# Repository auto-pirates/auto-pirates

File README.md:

# auto-pirates
*Autonomous Boat Project*

This repository contains the documentation of the Autonomous boat project.

You can find --

* Systems Engineering Presentations
* MRSD Presenatation
* Individual Lab Presentations 
* Critical Design Review

and other miscellaneous documents.

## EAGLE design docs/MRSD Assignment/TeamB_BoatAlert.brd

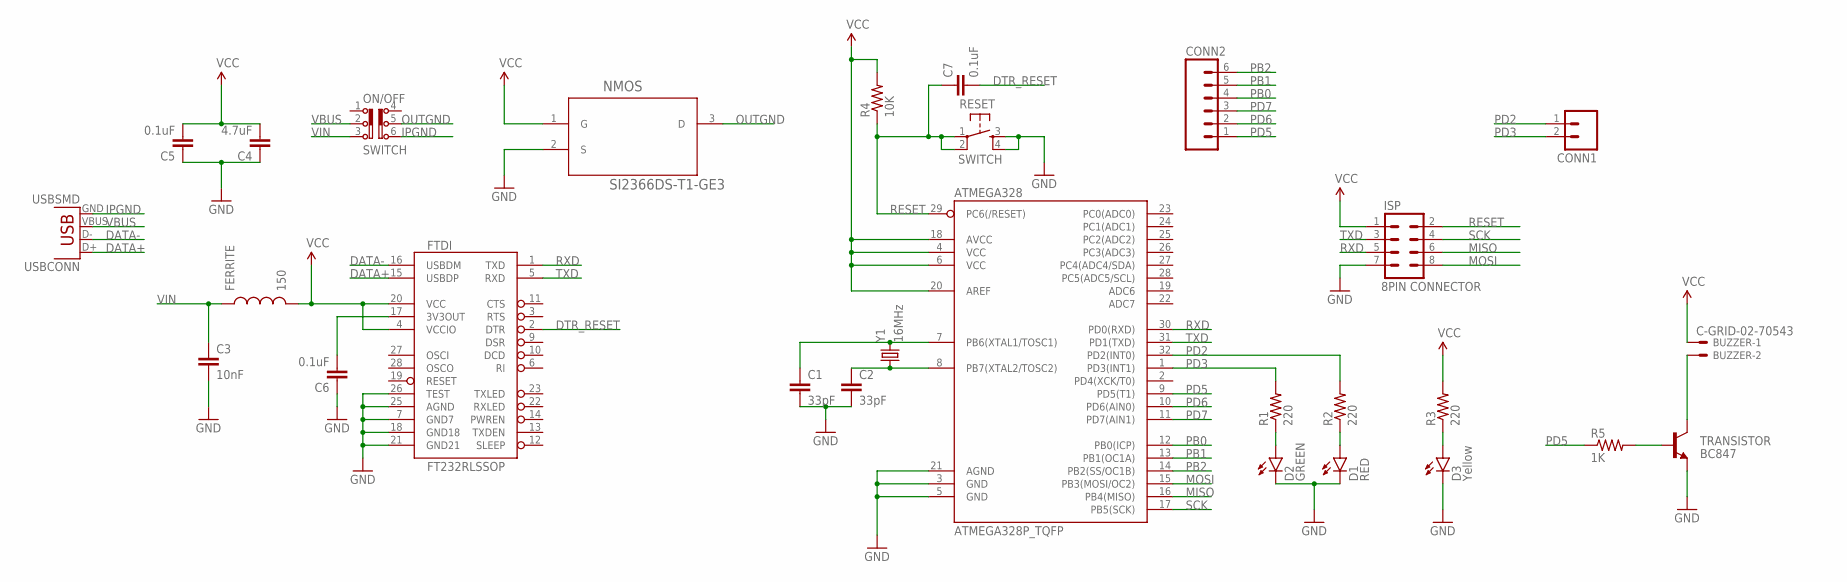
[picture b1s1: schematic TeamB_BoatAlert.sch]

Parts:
ATMEGA328: ATMEGA328P_TQFP; TQFP32-08
BUZZER: C-GRID-02-70543; 70543-02
C1, C2: 33pF; 0603-CAP
C3: 10nF; 0603-CAP
C4: 4.7uF; 0603-CAP
C5, C6, C7: 0.1uF; 0603-CAP
CONN1: M02LOCK; 1X02_LOCK
CONN2: M06LONGPADS; 1X06_LONGPADS
D1: RED; LED-0603
D2: GREEN; LED-0603
D3: Yellow; LED-0603
FERRITE: 150; 0805
FTDI: FT232RLSSOP; SSOP28DB
ISP: 8PIN CONNECTOR; 2X4
NMOS: SI2366DS-T1-GE3; SOT95P237X112-3N
ON/OFF: SWITCH; JS202011SCQN
R1, R2, R3: 220; 0805
R4: 10K; 0603-RES
R5: 1K; 0603-RES
RESET: SWITCH; 7914G
TRANSISTOR: BC847; SOT23-3
USBCONN: USBSMD; USB-MINIB
Y1: 16MHz; HC49UP

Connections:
DATA+: FTDI.15 (USBDP), USBCONN.D+
DATA-: FTDI.16 (USBDM), USBCONN.D-
DTR_RESET: C7.2, FTDI.2 (DTR)
GND: ATMEGA328.3 (GND), ATMEGA328.5 (GND), ATMEGA328.21 (AGND), C1.2, C2.2, C3.2, C4.1, C5.1, C6.1, D1.C, D2.C, D3.C, FTDI.7 (GND7), FTDI.18 (GND18), FTDI.21 (GND21), FTDI.25 (AGND), FTDI.26 (TEST), ISP.7, NMOS.2 (S), RESET.3, RESET.4, TRANSISTOR.2 (E)
IPGND: ON/OFF.6, USBCONN.GND
MISO: ATMEGA328.16 (PB4(MISO)), ISP.6
MOSI: ATMEGA328.15 (PB3(MOSI/OC2)), ISP.8
unnamed: ATMEGA328.7 (PB6(XTAL1/TOSC1)), C1.1, Y1.2
unnamed: ATMEGA328.8 (PB7(XTAL2/TOSC2)), C2.1, Y1.1
unnamed: D1.A, R2.1
unnamed: D2.A, R1.1
unnamed: BUZZER.2, TRANSISTOR.3 (C)
unnamed: D3.A, R3.1
unnamed: R5.2, TRANSISTOR.1 (B)
unnamed: C6.2, FTDI.17 (3V3OUT)
OUTGND: NMOS.3 (D), ON/OFF.5
PB0: ATMEGA328.12 (PB0(ICP)), CONN2.4
PB1: ATMEGA328.13 (PB1(OC1A)), CONN2.5
PB2: ATMEGA328.14 (PB2(SS/OC1B)), CONN2.6
PD2: ATMEGA328.32 (PD2(INT0)), CONN1.1, R2.2
PD3: ATMEGA328.1 (PD3(INT1)), CONN1.2, R1.2
PD5: ATMEGA328.9 (PD5(T1)), CONN2.1, R5.1
PD6: ATMEGA328.10 (PD6(AIN0)), CONN2.2
PD7: ATMEGA328.11 (PD7(AIN1)), CONN2.3
RESET: ATMEGA328.29 (PC6(/RESET)), C7.1, ISP.2, R4.1, RESET.1, RESET.2
RXD: ATMEGA328.30 (PD0(RXD)), FTDI.1 (TXD), ISP.5
SCK: ATMEGA328.17 (PB5(SCK)), ISP.4
TXD: ATMEGA328.31 (PD1(TXD)), FTDI.5 (RXD), ISP.3
VBUS: ON/OFF.2, USBCONN.VBUS
VCC: ATMEGA328.4 (VCC), ATMEGA328.6 (VCC), ATMEGA328.18 (AVCC), ATMEGA328.20 (AREF), BUZZER.1, C4.2, C5.2, FERRITE.2, FTDI.4 (VCCIO), FTDI.20 (VCC), ISP.1, NMOS.1 (G), R3.2, R4.2
VIN: C3.1, FERRITE.1, ON/OFF.3

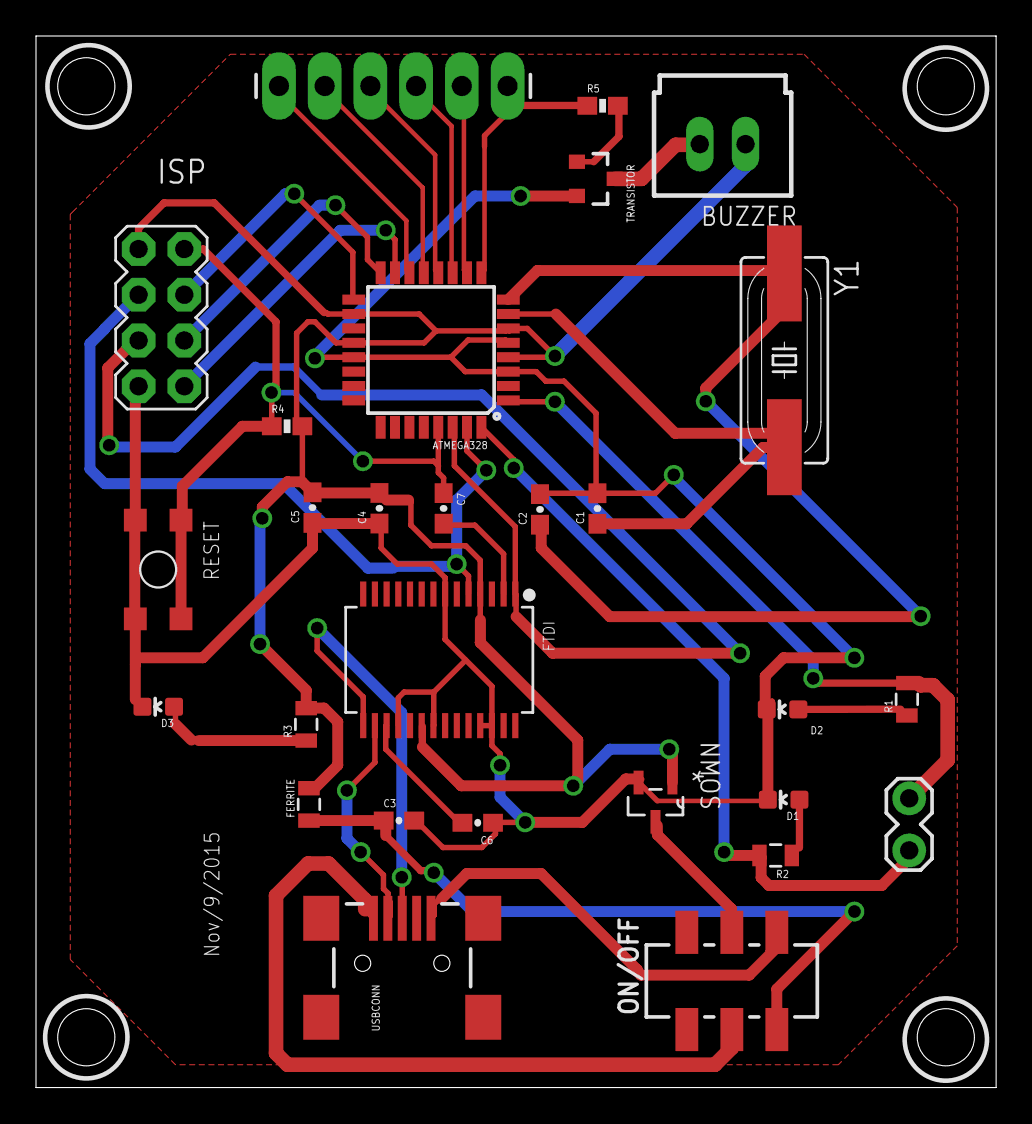
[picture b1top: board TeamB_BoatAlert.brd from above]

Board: 2 copper layers, 53.3 x 58.4 mm, 28 parts (0 on the bottom side), 31 nets.

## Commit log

2015-10-24 Added ILR2 and presentations
2015-11-24 hello
2015-11-24 Bikram's ILR added
2015-11-24 Systems second presentation uploaded
2015-11-24 PRs added
2015-11-26 ILR 5 -- bhanzra added
2015-11-26 Tushar and Will Mohan ILR added
2015-11-26 ILR 5 -- bhanzra added updated
2015-12-02 Added maps
2015-12-03 Added new files
2015-12-03 Added more stuff
2015-12-03 FVE docs added
2015-12-18 Added CDR and systems final presentation
2015-12-19 Added SecondTestPlan
2015-12-19 Added Issue Log
2016-01-29 Tushar_ILR06
2016-01-29 add william's ILR 6
2016-01-29 added TeamB_tk1_ILR06.pdf
2016-01-29 Added ILR06 -- bhanzra
2016-02-04 Issue Logs Updates
2016-02-04 Added third test plan
2016-02-04 Spring Updates PPT
2016-02-04 Added TestPlan
2016-02-05 Shiyu_ILR
2016-02-12 shiyuILR07
2016-02-12 ILR07 bikz05 added
2016-02-14 ILR_tchugh
2016-02-15 add wseto ILR07
2016-02-19 Added files via upload
2016-02-20 IssueLogsUpdated
2016-02-26 shiyuILR08
2016-02-26 Added ILR: Tushar
2016-02-26 Add tk1's ILR08.
2016-02-26 bikz05 ILR08 added
2016-02-29 add wseto ILR08
2016-02-29 SDR added
2016-03-18 Tushar_ILR09 added
2016-03-19 bikz05 ILR added
2016-03-23 Standards and Regulations ppt added
2016-03-26 add wseto ILR09
2016-04-01 add shiyu ILR09
2016-04-01 add shiyu ILR10
2016-04-01 Tushar_ILR10 added
2016-04-01 bikz05 ILR10.pdf added
2016-04-01 IssueLog_Updated
2016-04-02 add wseto ILR10
2016-04-06 SVE_TestPlan
2016-04-14 tchugh_ILR11_added
2016-04-15 bikz05 ILR11.pdf added
2016-05-05 Added poster
2016-05-05 add wseto ILR11
2016-05-05 Issue Logs Updated
2016-05-06 add shiyu ilr11
2016-05-06 Final Report Added

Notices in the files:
parts and their libraries:
SparkFun-DigitalIC: Licensing: Creative Commons ShareAlike 4.0 International - https://creativecommons.org/licenses/by-sa/4.0
switch-ck: Copyright (C) 2011, Bob Starr
